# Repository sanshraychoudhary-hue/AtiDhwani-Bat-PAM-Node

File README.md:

# AtiDhwani — ESP32-S3 Passive Acoustic Monitoring (PAM) Node & Ultrasonic Bat Detector

[-brightgreen.svg)](hardware/)

**AtiDhwani** (*अतिध्वनि* — *Sanskrit for Ultrasound / Supersonic sound*) is an open-source, high-performance, modular **Passive Acoustic Monitoring (PAM)** hardware node and handheld bat detector. 

Designed for wildlife ecologists, bioacoustic researchers, conservationists, and field naturalists, AtiDhwani captures, records, and transforms ultrasonic echolocation calls from microbats and orthopterans in the **10 kHz to 96 kHz** frequency spectrum in real time.

---

## Visual Preview (Hardware Revision v3.3 Compact — 98×98 mm)

| Top View (389 Routed Traces) | Bottom Layer (Power & Ground Pours) |
| :---: | :---: |
|  |  |

| 3D Perspective (Complete Board) | AD828 Preamp Sockets & Under-ESP32 Console |
| :---: | :---: |
|  |  |

| Overhanging Right Edge (Jack, SD, OLED) |
| :---: |
|  |

---

## 1. Why AtiDhwani?

Commercial ultrasonic bat detectors and long-term acoustic loggers (such as the Song Meter SM4BAT, Pettersson D1000X, or Wildlife Acoustics Echo Meter Touch) cost anywhere from **$300 to $3,500 USD**. Low-cost DIY alternatives often suffer from high noise floors, limited sampling bandwidth, or lack of direct real-time auditory feedback in the field.

**AtiDhwani bridges this gap:**
* **BOM Cost Under $40 USD:** Built entirely using readily available commodity modules, surface-mount MEMS transducers, and standard 2-layer FR-4 fabrication.
* **Sub-100mm Budget Carrier ($98.0 \times 98.0\text{ mm}$):** Optimized specifically to qualify for ultra-low-cost fabrication tiers (e.g. $2 JLCPCB / PCBWay specials) while preserving full mechanical clearance.
* **Dual-Stage Ultrasonic Front-End with AD828 Preamp:**
  * **Stage 1 (Bench testing & close roosts):** Direct AC-coupled output from Knowles & Infineon MEMS microphones into the WM8782 ADC.
  * **Stage 2 (Distant foraging bats outdoors):** Plug-in female header sockets for a dual-channel AD828 low-noise operational amplifier module (powered from regulated 5V VBUS), boosting faint, distant ultrasonic calls by 20–30 dB before digitization.
* **Under-ESP32 Audio Interconnect Console:** Direct female sockets for WM8782 ADC (`J_ADC1`), Preamp Out (`J_PREAMP_OUT`), and Mic Out (`J_MIC_OUT`) concentrated beneath the ESP32-S3 module, keeping high-speed 192 kHz I2S digital audio lines under 10 mm.
* **True 192 kHz 24-Bit Ultrasonic Capture:** External Wolfson WM8782 stereo ADC operating in hardware Master Mode with dedicated 24.576 MHz crystal oscillator.
* **Real-Time Heterodyne Listening:** Tunable local oscillator ($15\text{ kHz} - 90\text{ kHz}$) mixed directly in DSP, down-converting ultrasound to human-audible frequencies with zero latency.
* **Overhanging Field Peripherals:** 
  * MicroSD card slot and 3.5mm stereo headphone jack overhang the right PCB perimeter for effortless enclosure mounting.
  * 0.91" OLED display mounted vertically on the right perimeter for clear night-time status viewing.
  * Sockets for TP4056 USB-C charger and XL3608 5V step-up boost converter.

---

## 2. Key Specifications

| Subsystem | Specification |
| :--- | :--- |
| **Acoustic Range** | **10 kHz to 96 kHz** (Nyquist limit at 192 kHz sampling rate) |
| **Microphones** | Knowles SPV0142LR5H-1 ($10 - 80+\text{ kHz}$) + Infineon IM70A135 ($70\text{ dB(A)}$ SNR) |
| **Microphone Supply** | AP2127K-2.8 Ultra-Low-Noise LDO ($2.8\text{ V}$, high PSRR) |
| **Ultrasonic Preamp** | On-board female socket for AD828 Dual Op-Amp Module (3.8V–15V supply, 20–30 dB gain stage) |
| **Audio ADC** | Wolfson / Cirrus Logic WM8782 (24-bit, 192 kHz stereo, Master Clocked) |
| **Compute Engine** | ESP32-S3 Dual-Core Xtensa LX7 @ 240 MHz + **8MB Octal PSRAM (N16R8)** |
| **Audio DAC** | TI / Burr-Brown PCM5102A (32-bit, integrated charge pump, $2.1\text{ V}_{\text{RMS}}$ line/headphone out) |
| **Audio Outputs** | 3.5mm stereo headphone jack (overhanging right edge) + duplicate breakout headers |
| **Storage** | MicroSD slot (overhanging right edge, FAT32 filesystem, sustained DMA WAV logging) |
| **Display** | 0.91" 128×32 SSD1306 OLED (I2C at 400 kHz) |
| **User Controls** | 1× EC11 rotary encoder with push switch + 4× tactile buttons (Record, Display, Freq UP, Freq DOWN) |
| **Power Supply** | Single-cell 3.7V Li-Ion / 18650 battery via 2-pin JST-PH or header |
| **Charging & Boost** | On-board sockets for TP4056 (USB-C 1A) and XL3608 5V step-up boost module |
| **Telemetry** | Integrated 1:2 battery voltage divider ($100\text{ k}\Omega / 100\text{ k}\Omega \pm 1\%$) with $2.2\text{ nF}$ filter on GPIO2 |
| **PCB Dimensions** | **98.0 mm × 98.0 mm** (Sub-100mm tier, 2-layer FR-4, 1.6 mm thickness, 1 oz Cu, 0 DRC violations) |

---

## 3. System Architecture

```mermaid
flowchart TD
    subgraph Power["Power Subsystem"]
        BATT["3.7V Li-Ion Battery"] --> TP["TP4056 Charger (USB-C 5V 1A)"]
        TP --> SW["SPDT Power Switch"]
        SW --> BOOST["XL3608 5V Step-Up Boost"]
        SW --> GAUGE["100k/100k Divider + 2.2nF Filter"]
        BOOST --> V5["5V System Rail (VBUS)"]
        GAUGE --> IO2["ESP32-S3 GPIO 2 (ADC1)"]
    end

    subgraph Acoustic["Ultrasonic Front-End"]
        LDO["AP2127K-2.8V Low-Noise LDO"] --> MIC1["Knowles SPV0142 (10-80kHz)"]
        LDO --> MIC2["Infineon IM70A135 (High-SNR)"]
        MIC1 --> C1["2.2µF AC Coupling"]
        MIC2 --> C2["2.2µF AC Coupling"]
        C1 --> J_MIC["J_MIC_OUT (1x03 Header)"]
        C2 --> J_MIC
        J_MIC --> PREAMP["AD828 Op-Amp Preamp Module (Optional 20-30dB Boost)"]
        PREAMP --> J_PRE["J_PREAMP_OUT (1x03 Header)"]
        J_PRE --> ADC["WM8782 ADC (Master Mode, 192kHz / 24-bit)"]
        J_MIC -. "Direct Bypass (Stage 1)" .-> ADC
    end

    subgraph Core["ESP32-S3 Dual-Core Xtensa LX7 (240MHz, 8MB PSRAM)"]
        ADC -- "I2S RX (IO39 BICK, IO40 DATA, IO41 LRCK)" --> ESP["ESP32-S3 Core & DMA Engines"]
        ESP --> DSP["Real-Time DSP (Heterodyne, Div-by-N, FFT)"]
        ESP --> REC["FAT32 WAV File Writer (Ring Buffer)"]
    end

    subgraph UI_Right["User Interface & Peripherals (Right Overhang)"]
        ESP -- "I2C (IO8/SDA, IO9/SCK)" --> OLED["0.91-inch SSD1306 OLED (128x32)"]
        ESP -- "SPI (IO10-13)" --> SD["MicroSD Push-Push Slot"]
        DSP -- "I2S TX (IO15-17)" --> DAC["PCM5102A 32-Bit DAC"]
        DAC --> PHONE["3.5mm Headphone Jack"]
        ENC["EC11 Encoder (IO4-6)"] --> ESP
        BTNS["Tactile Buttons (IO1, 3, 7, 21)"] --> ESP
    end
```

---

## 4. Repository Structure

```text
├── assets/                  # High-resolution 3D CAD renders and photos
│   └── renders/             # Carrier top, iso, DAC zoom, and edge zoom images
├── docs/                    # In-depth engineering specifications
│   ├── ARCHITECTURE.md      # Full signal path, power tree, and DSP design
│   ├── PINOUT_REFERENCE.md  # Complete 44-pin ESP32-S3 and header netlist mapping
│   ├── ENCLOSURE_GUIDE.md   # Dimensions, port cutouts, and 3D printing clearances
│   ├── HARDWARE_AUDIT.md    # DRC logs, trace impedance, and layout revisions
│   └── datasheets/          # Sensor and component reference datasheets
├── firmware/                # Production embedded C++ firmware
│   ├── src/                 # Arduino sketch, DSP engines, and web companion
│   └── README.md            # Board setup, compiler flags, and flashing guide
├── hardware/                # KiCad 10 project and manufacturing files
│   ├── kicad/               # Schematics, PCB layout, and design rules
│   ├── gerbers/             # Fabrication zip, Gerber files, and NC drills
│   ├── schematic/           # Vector PDF schematic and high-res diagram
│   ├── bom/                 # Human-readable & CSV Bill of Materials
│   └── README.md            # PCB specs, layer stackup, and ordering guide
├── tests/                   # Modular hardware verification sketches
│   ├── test_01_esp32_psram/ # PSRAM throughput and memory test
│   ├── test_02_oled/        # I2C display test
│   ├── test_03_rotary_encoder/ # Quadrature encoder test
│   ├── test_04_buttons/     # Debounced button test
│   ├── test_05_sd_card/     # MicroSD SPI read/write speed test
│   ├── test_06_wm8782_adc/  # 192 kHz ADC I2S capture test
│   ├── test_07_pcm5102_dac/ # 48 kHz DAC I2S audio sweep test
│   ├── test_08_integrated_ui_sd/ # UI + SD card event logging
│   ├── test_esp32_ultrasonic_generator/ # 35-100 kHz PWM signal generator
│   ├── test_full_system_adc_dac_sd/     # End-to-end loopback test
│   ├── test_layer1_full_check/          # Comprehensive bus self-test
│   └── test_audio_samples/  # Real bat recordings and synthetic test chirps
├── .gitignore               # Clean git exclusion rules
├── LICENSE                  # MIT Open Source License
└── README.md                # Top-level repository overview (this document)
```

---

## 5. Getting Started

### 1. Order PCBs
Download the ready-to-fabricate gerber package from `hardware/gerbers/Esperdyne_Motherboard_Gerbers_v3.1.zip` and submit to your preferred PCB fabricator (JLCPCB, PCBWay, OSH Park).

### 2. Procure Components
Refer to [hardware/bom/BOM.md](hardware/bom/BOM.md) for the complete list of parts, module breakouts, and passives.

### 3. Flash Firmware
1. Open `firmware/src/Esperdyne_Full_Firmware.ino` in Arduino IDE or PlatformIO.
2. Select **ESP32S3 Dev Module** with **OPI PSRAM Enabled** and **USB CDC on Boot Enabled**.
3. Compile and flash via the USB Type-C port on the ESP32-S3 module.

### 4. Hardware Bring-Up
Follow the step-by-step verification guide in [tests/README.md](tests/README.md) using the standalone verification sketches (`test_01` through `test_08`).

---

## 6. Enclosure & 3D Printing

Revision v3.1 features optimized component orientations for seamless integration into custom 3D printed enclosures:
* **Headphone Jack:** Standard 3.5mm stereo jack accessible from the upper-right perimeter.
* **MicroSD Card:** Accessible from the right-hand side wall.
* **Power Switch & USB-C:** Power slide switch and TP4056 charging port accessible along the left perimeter.
* **Mounting:** 4× M3 corner mounting holes (hole centers at 5.0 mm inset).
* For detailed enclosure dimensions and cutout offsets, see [docs/ENCLOSURE_GUIDE.md](docs/ENCLOSURE_GUIDE.md).

---

## 7. License

This project is licensed under the **MIT License** — see the [LICENSE](LICENSE) file for details. You are free to build, modify, distribute, and commercialize this hardware and software.

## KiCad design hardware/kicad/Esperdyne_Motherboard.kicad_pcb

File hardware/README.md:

# AtiDhwani Bat PAM Motherboard Hardware (v3.3 Compact — Sub-100mm & AD828 Preamp)

Welcome to the hardware repository for the **AtiDhwani Bat PAM Node Carrier Motherboard (Revision v3.3 Compact)**. This carrier board integrates all ultrasonic acoustic front-ends, high-speed digital audio converters, power management, storage, and user interface modules onto a single 2-layer PCB designed and verified in KiCad 10 (389 copper segments, 14 vias, 52/52 nets routed, 0 DRC violations).

Revision v3.3 introduces a shrunk **98.0 mm × 98.0 mm** board outline that fits within standard budget prototyping tiers (e.g., $2 for 5 boards at JLCPCB/PCBWay), adds dedicated female header pin sockets for the popular **AD828 stereo op-amp preamplifier module** to capture distant bat calls, and consolidates all audio interconnects directly beneath the ESP32-S3 module.

---

## 1. PCB Specifications

| Parameter | Specification | Notes |
| :--- | :--- | :--- |
| **Dimensions** | **98.0 mm × 98.0 mm** (3.86" × 3.86") | Strictly under 100mm to qualify for manufacturer budget tiers |
| **Layer Count** | 2 Layers (Top & Bottom Copper) | Standard, low-cost fabrication stackup |
| **Routing Status** | **100% Routed (52 / 52 Nets)** | 389 copper trace segments, 14 centered vias |
| **Board Thickness** | 1.6 mm standard FR-4 | High mechanical rigidity for field deployment |
| **Copper Weight** | 1 oz / 35 µm outer layers | Optimized for power distribution and low-impedance grounds |
| **Surface Finish** | HASL Lead-Free or ENIG | ENIG recommended for MEMS microphone acoustic port reflow |
| **Minimum Trace/Space** | 0.25 mm / 0.25 mm (10 mil / 10 mil) | Standard fab house capability (JLCPCB / PCBWay) |
| **Minimum Drill** | 0.3 mm (via) / 0.8 mm (component pins) | Fabricator compliant |
| **Solder Mask** | Dark Green | High contrast for white silkscreen inspection |
| **Silkscreen** | White | Full pin labels, jumper notes, and component reference designators |
| **Mounting Holes** | 4 × M3 (3.2 mm drill, 6.0 mm clearance) | Located at PCB corners with 5.0 mm edge inset (105, 105 to 193, 193) |

---

## 2. Directory Structure

```text
hardware/
├── kicad/                               # Native KiCad 10 project files
│   ├── Esperdyne_Motherboard.kicad_pro  # KiCad Project File
│   ├── Esperdyne_Motherboard.kicad_sch  # Complete Hierarchical Schematic
│   ├── Esperdyne_Motherboard.kicad_pcb  # Fully Routed PCB Layout (389 tracks, 14 vias)
│   ├── Esperdyne_Motherboard.kicad_dru  # KiCad Design Rules
│   ├── Esperdyne_Motherboard.kicad_prl  # Project Local Settings
│   ├── sym-lib-table                    # Symbol Library Table
│   └── fp-lib-table                     # Footprint Library Table
├── gerbers/                             # Production fabrication outputs
│   ├── Esperdyne_Motherboard_v3.3_Compact_Gerbers.zip # Ready-to-upload JLCPCB/PCBWay Zip
│   ├── *.gbr                            # Standard Gerber layer extensions
│   └── *.drl                            # Drill files (Excellon NC format)
├── schematic/                           # Production schematics & prints
│   ├── Esperdyne_Schematic_v3.3.pdf     # Vector PDF schematic with pinout callouts
│   └── schematic_render_v3.3.png        # High-res graphical schematic overview
└── bom/                                 # Bill of Materials
    ├── BOM.md                           # Human-readable markdown BOM with component suppliers
    └── BOM.csv                          # CSV export for automated purchasing / distributor cart import
```

---

## 3. Subsystem Breakdown

### Acoustic Bay (Left Side)
* **MEMS Transducers (`U2`, `U3`):**
  * Knowles SPV0142LR5H-1 wideband acoustic sensor ($10\text{ kHz} - 80+\text{ kHz}$).
  * Infineon IM70A135 ultra-high SNR ($70\text{ dB(A)}$) low-distortion sensor.
* **Acoustic LDO Regulator (`U4`):**
  * AP2127K-2.8V ultra-low-noise linear regulator isolated from digital switching ripple.
* **AD828 Operational Amplifier Preamp Sockets (`MOD_AD828`):**
  * Dedicated female header sockets matching standard AD828 dual-channel preamp modules ($33\text{ mm} \times 26.15\text{ mm}$):
    * Audio In (3-pin): `MIC1_OUT`, `GND`, `MIC2_OUT`.
    * Audio Out (3-pin): `PREAMP_OUT_L`, `GND`, `PREAMP_OUT_R`.
    * Power (2-pin): `VBUS` (+5.0V regulated), `GND`.
  * Provides selectable 20–30 dB gain stage for capturing faint ultrasonic bat calls at long distances outdoors.
* **Under-ESP32 Audio Interconnect Console:**
  * `J_ADC1`: 1×06 female header accepting the Wolfson WM8782 Master-Mode 192 kHz audio ADC breakout.
  * `J_PREAMP_OUT`: 1×03 female header breaking out amplified L/R signals.
  * `J_MIC_OUT`: 1×03 female header breaking out direct AC-coupled microphone signals.
  * Allows instantaneous jumper selection between direct mic feed (Stage 1) and preamp boost (Stage 2).

### Audio Conversion & Processing
* **32-Bit Stereo DAC Socket (`J_DAC1` & `J_DAC2`):**
  * Dual-header socket configuration matching the purple PCM5102A breakout overhanging the right perimeter:
    * `J_DAC1`: 1×06 horizontal female header along the bottom edge (`rot = 90`).
    * `J_DAC2`: 1×09 vertical female header along the left edge (`rot = 180`).
    * Hardware configuration jumpers: `H1L=GND` (FLT), `H2L=GND` (DEMP), `H3L=3.3V` (XSMT soft un-mute), `H4L=GND` (FMT standard I2S).
    * Integrated 3.5mm stereo headphone jack oriented outwards across the right PCB edge.
* **Microcontroller Sockets (`J_ESP_L1`, `J_ESP_R1`):**
  * Dual 1×22 2.54mm female sockets accepting the ESP32-S3 DevKitC-1 (N16R8 / N8R8).
  * Accompanied by duplicate 1×22 breakout headers (`J_ESP_L2`, `J_ESP_R2`) for full oscilloscope and logic analyzer probing.

### Power & Telemetry Bay (Lower Left)
* **TP4056 Li-Ion Charger Socket (`J_TP4056_IN` & `J_TP4056_OUT`):**
  * 4-pin corner-stand layout for plug-in TP4056 USB-C charging module.
* **XL3608 5V Step-Up Boost Socket (`J_BOOST_IN` & `J_BOOST_OUT`):**
  * 4-pin rectangular header layout supporting the micro boost module.
* **Power Control & Battery In:**
  * `J_BAT_IN`: 2-pin JST-PH / 2.54mm header for 3.7V 18650/LiPo cell.
  * `SW_PWR1`: 1×03 SPDT slide switch for hard power disconnection.
  * Precision 1:2 battery voltage divider ($100\text{ k}\Omega / 100\text{ k}\Omega \pm 1\%$) with a $2.2\text{ nF}$ ceramic filter feeding GPIO2 ADC1.

### User Interface & Storage Bay (Right Side Overhang)
* **MicroSD Push-Push Socket (`J_SD1`):**
  * 1×09 female socket oriented with the card insertion slot facing outwards past the right PCB edge.
* **0.91" I2C OLED Display Socket (`J_OLED1`):**
  * 1×04 vertical socket holding the screen on the right board boundary.
* **EC11 Rotary Encoder (`SW_ENC1`):**
  * 5-pin footprint with integrated push-to-click button for rapid heterodyne tuning and menu navigation.
* **Field Buttons (`SW1` - `SW4`):**
  * Four tactile 6×6 mm momentary switches for Record, Display Mode, Frequency UP, and Frequency DOWN.

---

## 4. Fabrication Guide

To order boards from JLCPCB, PCBWay, or any standard PCB manufacturer:
1. Download the pre-built zip file:
   `hardware/gerbers/Esperdyne_Motherboard_v3.3_Compact_Gerbers.zip`
2. Upload the `.zip` archive to your fabricator's online instant quote tool.
3. Select standard options:
   * **Base Material:** FR-4 (TG 130-140)
   * **Dimensions:** 98.0 mm × 98.0 mm (qualifies for budget $\le 100\text{ mm}$ special pricing)
   * **Layers:** 2
   * **Thickness:** 1.6 mm
   * **Copper Weight:** 1 oz
   * **Surface Finish:** Lead-Free HASL (or ENIG for easier MEMS soldering)
   * **Solder Mask:** Green (or your preferred color)
   * **Silkscreen:** White
4. KiCad Design Rule Check (DRC) report status: **0 Unconnected Pads, 0 Clearance Errors, 0 Hole Clearance Errors, 0 Courtyard Overlaps**.

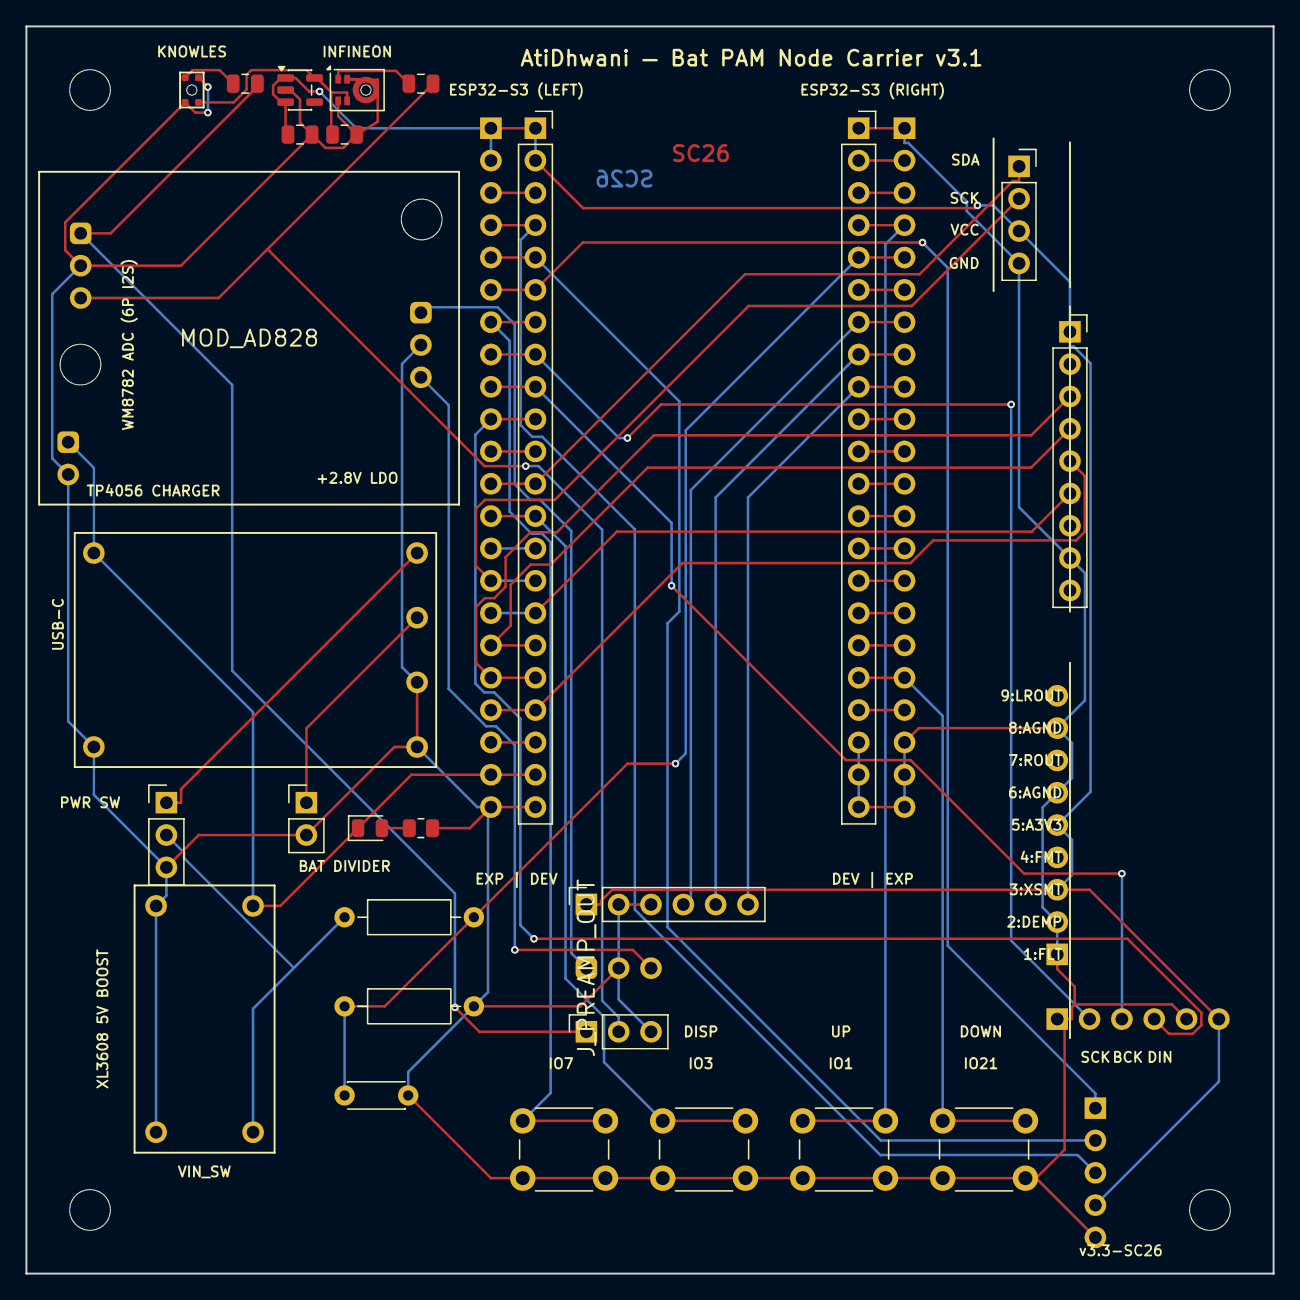
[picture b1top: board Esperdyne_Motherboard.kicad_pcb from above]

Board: 2 copper layers, 98.0 x 98.0 mm, 37 parts (0 on the bottom side), 50 nets.

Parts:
C1: 1uF_10V; C_0805_2012Metric
C2: 2.2uF_10V; C_0805_2012Metric
C_FILT: 2.2nF_222; C_Disc_D4.3mm_W1.9mm_P5.00mm
C_INF: 2.2uF_AC; C_0805_2012Metric
C_KNW: 2.2uF_AC; C_0805_2012Metric
D1: PWR_LED; LED_0805_2012Metric
H1, H2, H3, H4: MountingHole_M3; MountingHole_3.2mm_M3
J_ADC1: WM8782_ADC_6P; PinSocket_1x06_P2.54mm_Vertical
J_BATT: Battery_Input_2P; PinHeader_1x02_P2.54mm_Vertical
J_BOOST: XL3608_Boost_5V; XL3608_Mini_Boost_5V
J_DAC1: PCM5102A_DAC_I2S; PinSocket_1x06_P2.54mm_Vertical
J_DAC2: PCM5102A_DAC_CFG_OUT; PinSocket_1x09_P2.54mm_Vertical
J_ENC1: EC11_Encoder_Socket; PinSocket_1x05_P2.54mm_Vertical
J_ESP_L1: ESP32_DevKit_Left; PinSocket_1x22_P2.54mm_Vertical
J_ESP_L2: ESP32_Left_Breakout; PinSocket_1x22_P2.54mm_Vertical
J_ESP_R1: ESP32_DevKit_Right; PinSocket_1x22_P2.54mm_Vertical
J_ESP_R2: ESP32_Right_Breakout; PinSocket_1x22_P2.54mm_Vertical
J_MIC_OUT: Mic_Direct_Audio_Out; PinSocket_1x03_P2.54mm_Vertical
J_OLED1: OLED_0.91_SSD1306; PinSocket_1x04_P2.54mm_Vertical
J_PREAMP_OUT: Preamp_Audio_Out; PinSocket_1x03_P2.54mm_Vertical
J_SPI1: MicroSD_PCBCupid_9P; PinSocket_1x09_P2.54mm_Vertical
J_TP4056: TP4056_Module; TP4056_TypeC_5V_1A
MIC_INF: IM70A135_SMT; Infineon_PG-LLGA-5-1
MIC_KNW: Knowles_SPV0142; Knowles_SPV0142LR5H-1_2.75x1.85mm
MOD_AD828: AD828_Preamp_Module
R_DIV1, R_DIV2: 100k_1%; R_Axial_DIN0207_L6.3mm_D2.5mm_P10.16mm_Horizontal
R_LED: 1k_0805; R_0805_2012Metric
SW1: REC_IO7; SW_PUSH_6mm_H5mm
SW2: DISP_IO3; SW_PUSH_6mm_H5mm
SW3: UP_IO1; SW_PUSH_6mm_H5mm
SW4: DOWN_IO21; SW_PUSH_6mm_H5mm
SW_PWR: SPDT_Power_Switch; PinHeader_1x03_P2.54mm_Vertical
U4: AP2127K-2.8; SOT-23-5

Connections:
+2.8V: C2.1, MIC_INF.4, MIC_KNW.4, U4.5
+3.3V: C1.1, J_ADC1.1, J_DAC1.6, J_DAC2.3, J_DAC2.5, J_ENC1.4, J_ESP_L1.1, J_ESP_L1.2, J_ESP_L2.1, J_ESP_L2.2, J_OLED1.3, J_SPI1.1, U4.1, U4.3
BAT+: J_BATT.1, J_TP4056.4
EN: J_ESP_L1.3, J_ESP_L2.3
GND: C1.2, C2.2, C_FILT.2, J_ADC1.2, J_ADC1.3, J_BATT.2, J_BOOST.1, J_BOOST.3, J_DAC1.1, J_DAC1.5, J_DAC2.1, J_DAC2.2, J_DAC2.4, J_DAC2.6, J_DAC2.8, J_ENC1.5, J_ESP_L1.22, J_ESP_L2.22, J_ESP_R1.1, J_ESP_R1.20, J_ESP_R1.21, J_ESP_R1.22, J_ESP_R2.1, J_ESP_R2.20, J_ESP_R2.21, J_ESP_R2.22, J_MIC_OUT.3, J_OLED1.4, J_PREAMP_OUT.2, J_SPI1.8, J_TP4056.2, J_TP4056.5, J_TP4056.6, MIC_INF.2, MIC_INF.3, MIC_INF.5, MIC_KNW.2, MIC_KNW.3, MOD_AD828.2, MOD_AD828.5, MOD_AD828.8, R_DIV2.2, R_LED.2, SW1.2, SW2.2, SW3.2, SW4.2, SW_PWR.3, U4.2
IO0: J_ESP_R1.14, J_ESP_R2.14
IO1: J_ESP_R1.4, J_ESP_R2.4, SW3.1
IO2: C_FILT.1, J_ESP_R1.5, J_ESP_R2.5, R_DIV1.2, R_DIV2.1
IO3: J_ESP_L1.13, J_ESP_L2.13, SW2.1
IO4: J_ENC1.3, J_ESP_L1.4, J_ESP_L2.4
IO5: J_ENC1.2, J_ESP_L1.5, J_ESP_L2.5
IO6: J_ENC1.1, J_ESP_L1.6, J_ESP_L2.6
IO7: J_ESP_L1.7, J_ESP_L2.7, SW1.1
IO8: J_ESP_L1.12, J_ESP_L2.12, J_OLED1.1
IO9: J_ESP_L1.15, J_ESP_L2.15, J_OLED1.2
IO10: J_ESP_L1.16, J_ESP_L2.16, J_SPI1.6
IO11: J_ESP_L1.17, J_ESP_L2.17, J_SPI1.4
IO12: J_ESP_L1.18, J_ESP_L2.18, J_SPI1.3
IO13: J_ESP_L1.19, J_ESP_L2.19, J_SPI1.5
IO14: J_ESP_L1.20, J_ESP_L2.20
IO15: J_DAC1.2, J_ESP_L1.8, J_ESP_L2.8
IO16: J_DAC1.3, J_ESP_L1.9, J_ESP_L2.9
IO17: J_DAC1.4, J_ESP_L1.10, J_ESP_L2.10
IO18: J_ESP_L1.11, J_ESP_L2.11
IO20: J_ESP_R1.19, J_ESP_R2.19
IO21: J_ESP_R1.18, J_ESP_R2.18, SW4.1
IO35: J_ESP_R1.13, J_ESP_R2.13
IO36: J_ESP_R1.12, J_ESP_R2.12
IO37: J_ESP_R1.11, J_ESP_R2.11
IO38: J_ESP_R1.10, J_ESP_R2.10
IO39: J_ADC1.6, J_ESP_R1.9, J_ESP_R2.9
IO40: J_ADC1.5, J_ESP_R1.8, J_ESP_R2.8
IO41: J_ADC1.4, J_ESP_R1.7, J_ESP_R2.7
IO42: J_ESP_R1.6, J_ESP_R2.6
IO43: J_ESP_R1.2, J_ESP_R2.2
IO44: J_ESP_R1.3, J_ESP_R2.3
IO45: J_ESP_R1.15, J_ESP_R2.15
IO46: J_ESP_L1.14, J_ESP_L2.14
IO47: J_ESP_R1.17, J_ESP_R2.17
IO48: J_ESP_R1.16, J_ESP_R2.16
MIC1_OUT: C_KNW.2, J_MIC_OUT.1, MOD_AD828.1
MIC2_OUT: C_INF.2, J_MIC_OUT.2, MOD_AD828.3
MIC_INF_OUT: C_INF.1, MIC_INF.1
MIC_KNW_OUT: C_KNW.1, MIC_KNW.1
NET_LED_R: D1.2, R_LED.1
PREAMP_OUT_L: J_PREAMP_OUT.1, MOD_AD828.4
PREAMP_OUT_R: J_PREAMP_OUT.3, MOD_AD828.6
TP4056_OUT+: J_TP4056.3, SW_PWR.1
VBUS: D1.1, J_BOOST.4, J_ESP_L1.21, J_ESP_L2.21, J_TP4056.1, MOD_AD828.7
V_BATT_SW: J_BOOST.2, R_DIV1.1, SW_PWR.2
